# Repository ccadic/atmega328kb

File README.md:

# atmega328kb
Small computer KB for ATMEGA328P-AU

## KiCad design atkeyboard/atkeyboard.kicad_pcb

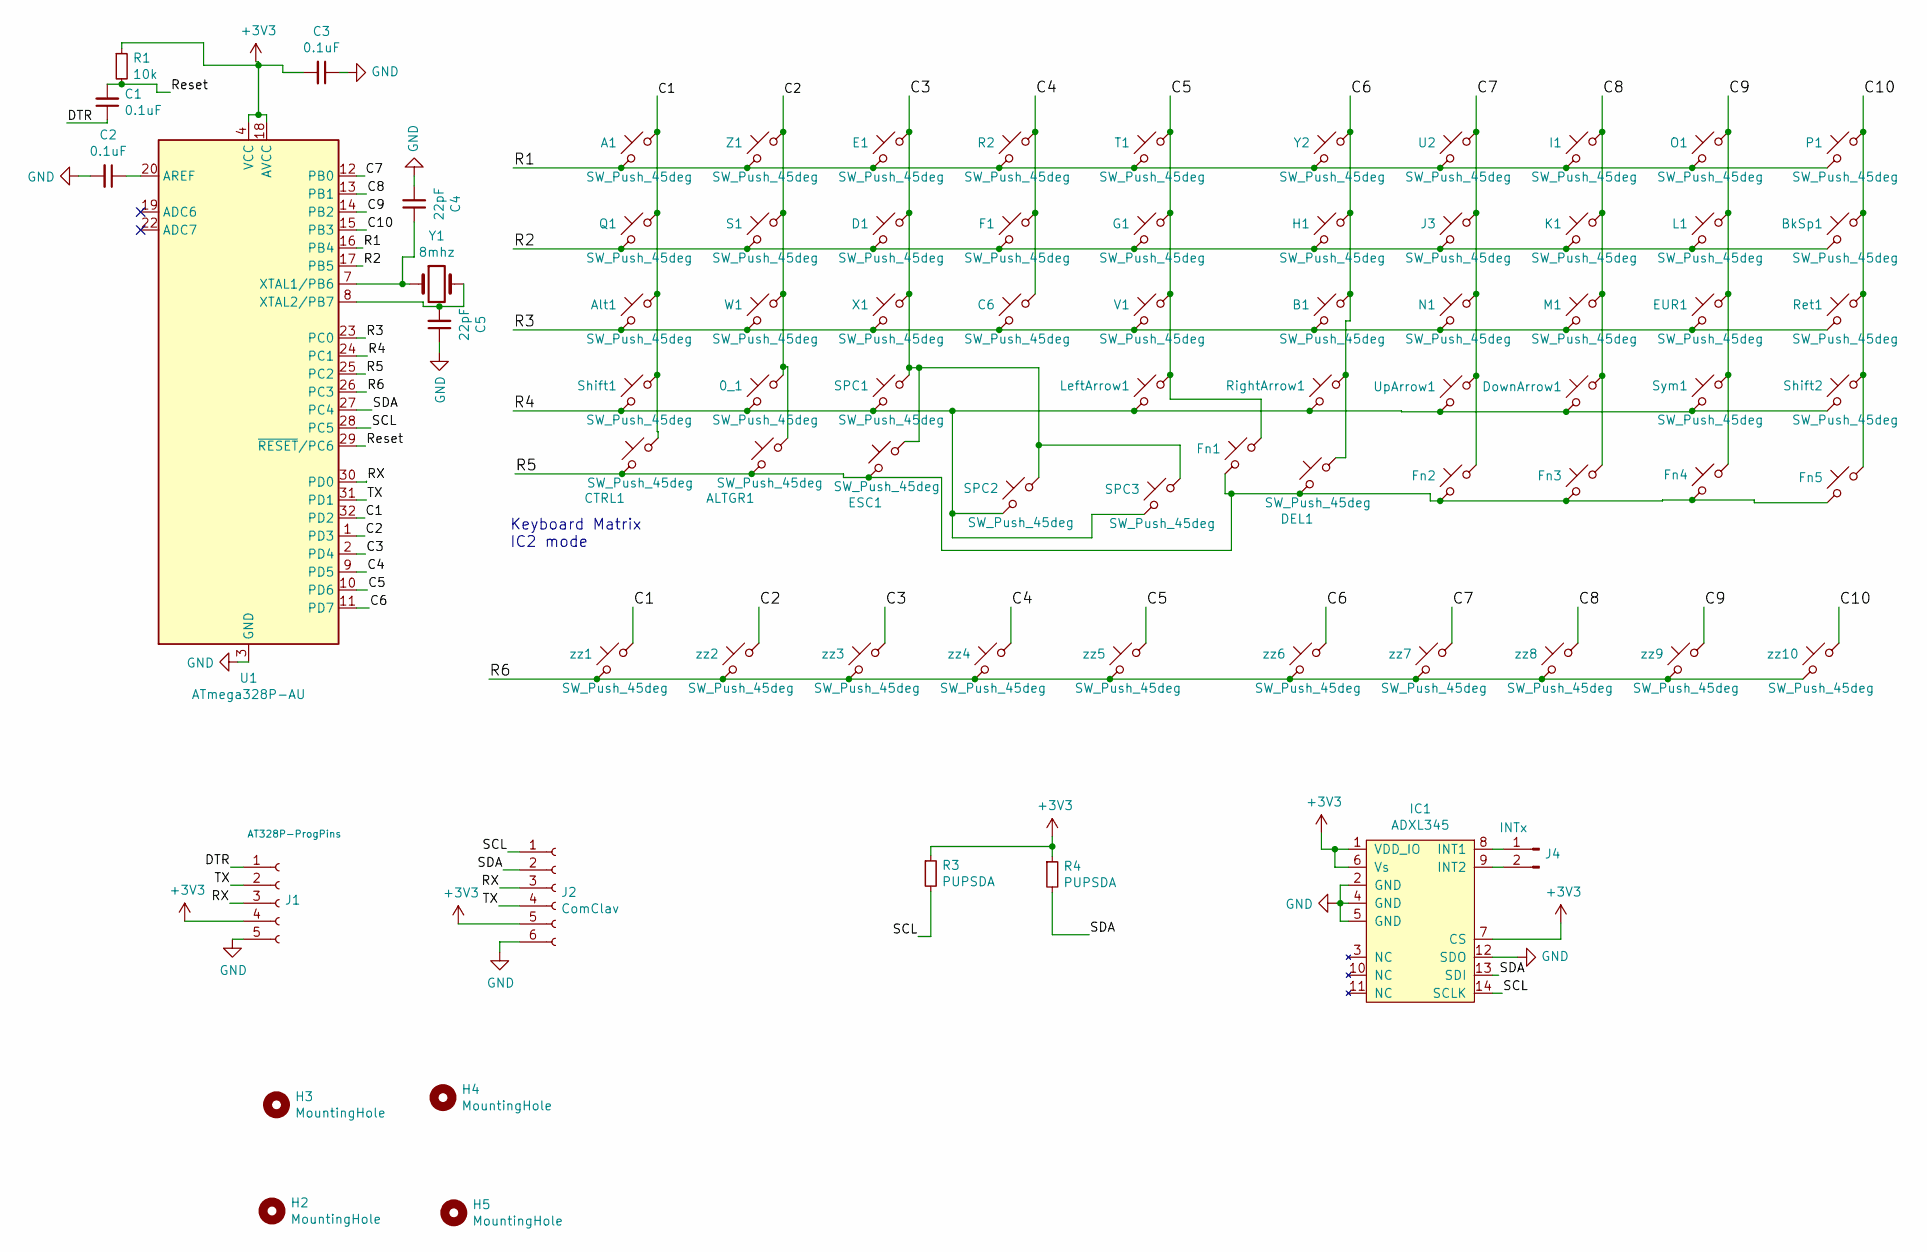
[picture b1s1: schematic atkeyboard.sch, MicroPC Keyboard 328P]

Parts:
0_1: SW_Push_45deg; SW_TP1003
A1: SW_Push_45deg; SW_TP1003
ALTGR1: SW_Push_45deg; SW_TP1003
Alt1: SW_Push_45deg; SW_TP1003
B1: SW_Push_45deg; SW_TP1003
BkSp1: SW_Push_45deg; SW_TP1003
C1, C2, C3: 0.1uF; C_0805_HandSoldering
C4, C5: 22pF; C_0805_HandSoldering
C6: SW_Push_45deg; SW_TP1003
CTRL1: SW_Push_45deg; SW_TP1003
D1: SW_Push_45deg; SW_TP1003
DEL1: SW_Push_45deg; SW_TP1003
DownArrow1: SW_Push_45deg; SW_TP1003
E1: SW_Push_45deg; SW_TP1003
ESC1: SW_Push_45deg; SW_TP1003
EUR1: SW_Push_45deg; SW_TP1003
F1: SW_Push_45deg; SW_TP1003
Fn1, Fn2, Fn3, Fn4, Fn5: SW_Push_45deg; SW_TP1003
G1: SW_Push_45deg; SW_TP1003
H1: SW_Push_45deg; SW_TP1003
H2, H3, H4, H5: MountingHole; MountingHole_2.2mm_M2_ISO7380
I1: SW_Push_45deg; SW_TP1003
IC1: ADXL345; Farnell 1853935
J1: AT328P-ProgPins; 4prog
J2: ComClav; 6prog
J3: SW_Push_45deg; SW_TP1003
J4: INTx; 2PADS
K1: SW_Push_45deg; SW_TP1003
L1: SW_Push_45deg; SW_TP1003
LeftArrow1: SW_Push_45deg; SW_TP1003
M1: SW_Push_45deg; SW_TP1003
N1: SW_Push_45deg; SW_TP1003
O1: SW_Push_45deg; SW_TP1003
P1: SW_Push_45deg; SW_TP1003
Q1: SW_Push_45deg; SW_TP1003
R1: 10k; R_0805_HandSoldering
R2: SW_Push_45deg; SW_TP1003
R3, R4: PUPSDA; R_0805_HandSoldering
Ret1: SW_Push_45deg; SW_TP1003
RightArrow1: SW_Push_45deg; SW_TP1003
S1: SW_Push_45deg; SW_TP1003
SPC1, SPC2, SPC3: SW_Push_45deg; SW_TP1003
Shift1, Shift2: SW_Push_45deg; SW_TP1003
Sym1: SW_Push_45deg; SW_TP1003
T1: SW_Push_45deg; SW_TP1003
U1: ATmega328P-AU; LQFP-32_7x7mm_Pitch0.8mm
U2: SW_Push_45deg; SW_TP1003
UpArrow1: SW_Push_45deg; SW_TP1003
V1: SW_Push_45deg; SW_TP1003
W1: SW_Push_45deg; SW_TP1003
X1: SW_Push_45deg; SW_TP1003
Y1: 8mhz; Crystal_SMD_HC49-SD
Y2: SW_Push_45deg; SW_TP1003
Z1: SW_Push_45deg; SW_TP1003
zz1, zz2, zz3, zz4, zz5, zz6, zz7, zz8, zz9, zz10: SW_Push_45deg; SW_TP1003

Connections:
+3V3: C3.2, IC1.1 (VDD_IO), IC1.6 (Vs), IC1.7 (CS), J1.4, J2.5, R1.1, R3.1, R4.1, U1.4 (VCC), U1.6 (VCC), U1.18 (AVCC)
/C1: A1.1, Alt1.1, CTRL1.1, Q1.1, Shift1.1, U1.32 (PD2), zz1.1
/C2: 0_1.1, ALTGR1.1, S1.1, U1.1 (PD3), W1.1, Z1.1, zz2.1
/C3: D1.1, E1.1, ESC1.1, SPC1.1, SPC2.1, SPC3.1, U1.2 (PD4), X1.1, zz3.1
/C4: C6.1, F1.1, R2.1, U1.9 (PD5), zz4.1
/C5: Fn1.1, G1.1, LeftArrow1.1, T1.1, U1.10 (PD6), V1.1, zz5.1
/C6: B1.1, DEL1.1, H1.1, RightArrow1.1, U1.11 (PD7), Y2.1, zz6.1
/C7: Fn2.1, J3.1, N1.1, U1.12 (PB0), U2.1, UpArrow1.1, zz7.1
/C8: DownArrow1.1, Fn3.1, I1.1, K1.1, M1.1, U1.13 (PB1), zz8.1
/C9: EUR1.1, Fn4.1, L1.1, O1.1, Sym1.1, U1.14 (PB2), zz9.1
/C10: BkSp1.1, Fn5.1, P1.1, Ret1.1, Shift2.1, U1.15 (PB3), zz10.1
/DTR: C1.1, J1.1
/R1: A1.2, E1.2, I1.2, O1.2, P1.2, R2.2, T1.2, U1.16 (PB4), U2.2, Y2.2, Z1.2
/R2: BkSp1.2, D1.2, F1.2, G1.2, H1.2, J3.2, K1.2, L1.2, Q1.2, S1.2, U1.17 (PB5)
/R3: Alt1.2, B1.2, C6.2, EUR1.2, M1.2, N1.2, Ret1.2, U1.23 (PC0), V1.2, W1.2, X1.2
/R4: 0_1.2, DownArrow1.2, LeftArrow1.2, RightArrow1.2, SPC1.2, SPC2.2, SPC3.2, Shift1.2, Shift2.2, Sym1.2, U1.24 (PC1), UpArrow1.2
/R5: ALTGR1.2, CTRL1.2, DEL1.2, ESC1.2, Fn1.2, Fn2.2, Fn3.2, Fn4.2, Fn5.2, U1.25 (PC2)
/R6: U1.26 (PC3), zz1.2, zz2.2, zz3.2, zz4.2, zz5.2, zz6.2, zz7.2, zz8.2, zz9.2, zz10.2
/RX: J1.3, J2.3, U1.30 (PD0)
/Reset: C1.2, R1.2, U1.29 (~RESET~/PC6)
/SCL: IC1.14 (SCLK), J2.1, R3.2, U1.28 (PC5)
/SDA: IC1.13 (SDI), J2.2, R4.2, U1.27 (PC4)
/TX: J1.2, J2.4, U1.31 (PD1)
GND: C2.2, C3.1, C4.2, C5.1, IC1.2 (GND), IC1.4 (GND), IC1.5 (GND), IC1.12 (SDO), J1.5, J2.6, U1.3 (GND), U1.5 (GND), U1.21 (GND)
unnamed: C2.1, U1.20 (AREF)
unnamed: C4.1, U1.7 (XTAL1/PB6), Y1.1
unnamed: C5.2, U1.8 (XTAL2/PB7), Y1.2
unnamed: IC1.8 (INT1), J4.1
unnamed: IC1.9 (INT2), J4.2

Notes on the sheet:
Keyboard Matrix IC2 mode

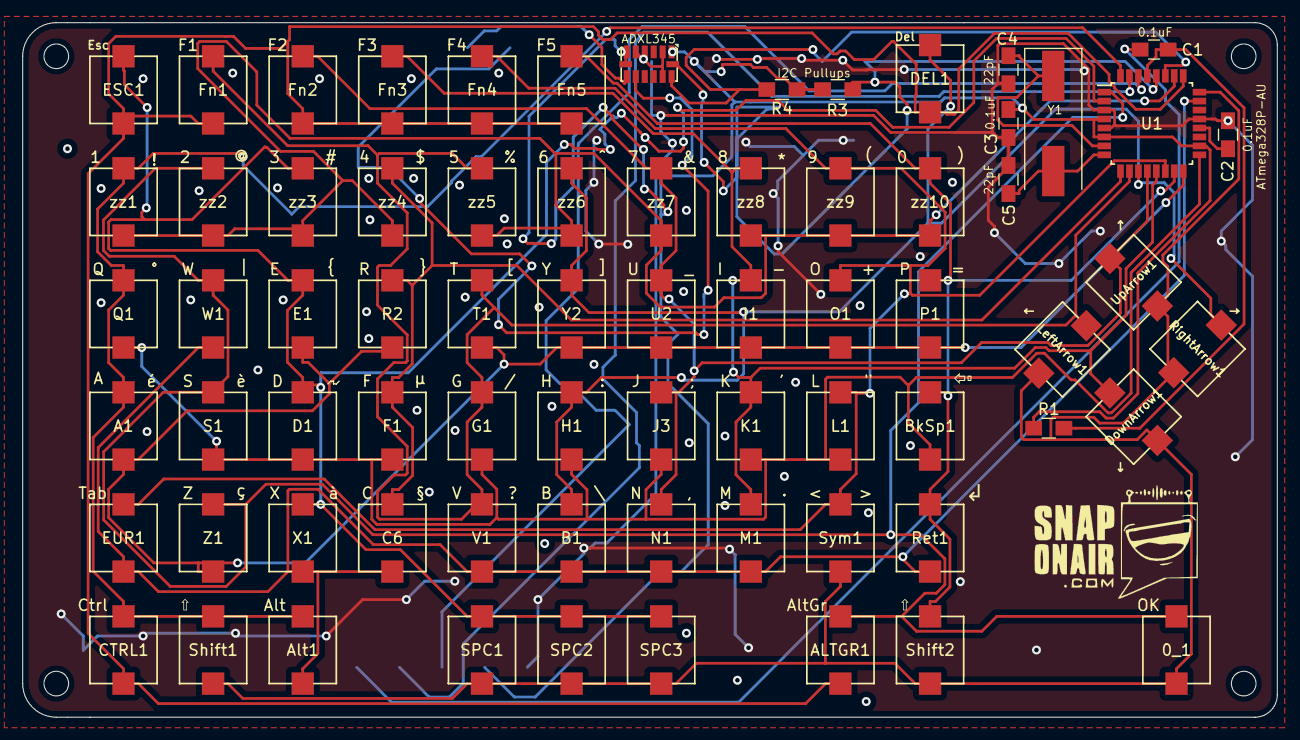
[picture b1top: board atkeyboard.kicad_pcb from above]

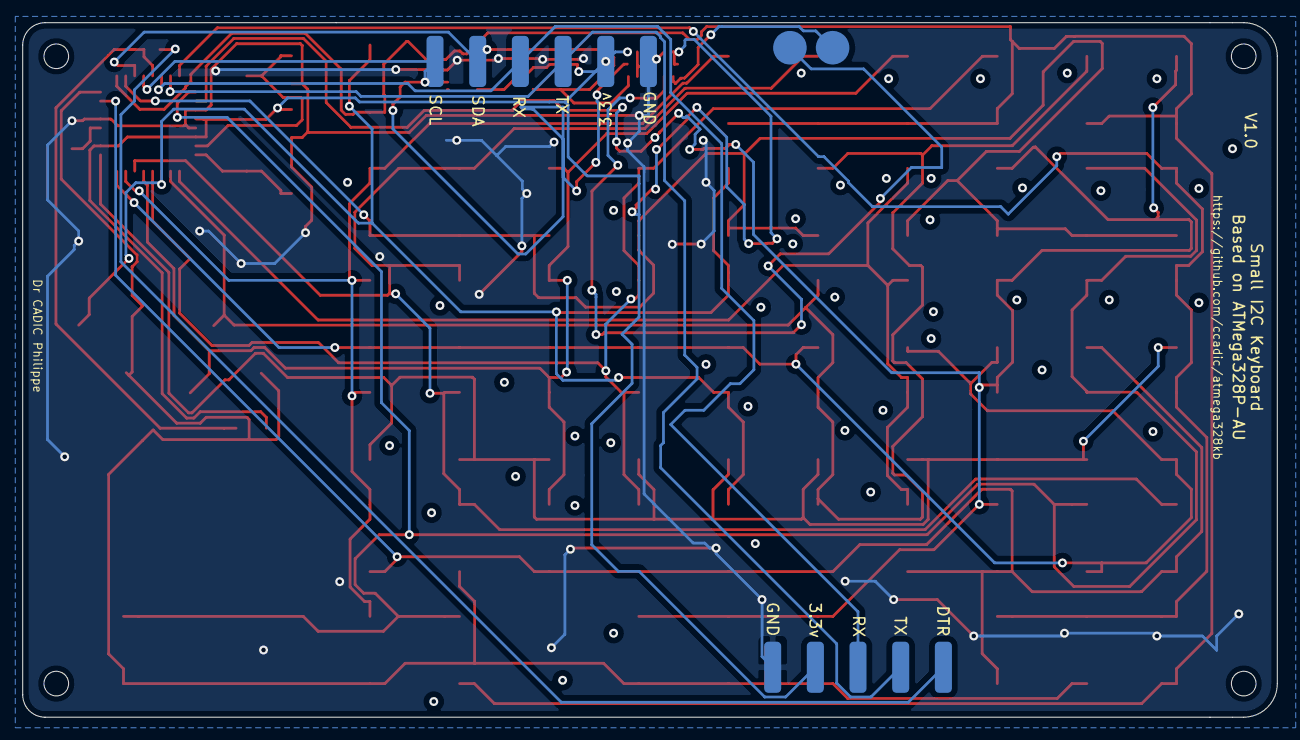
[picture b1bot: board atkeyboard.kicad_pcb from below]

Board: 2 copper layers, 112.0 x 62.0 mm, 78 parts (3 on the bottom side), 29 nets.
